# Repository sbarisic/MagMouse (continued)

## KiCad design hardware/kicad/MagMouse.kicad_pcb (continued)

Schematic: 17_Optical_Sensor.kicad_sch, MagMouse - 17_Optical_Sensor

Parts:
C80, C86, C87: 100nF; C_0603_1608Metric; MPN CC0603KRX7R9BB104; LCSC C14663
R131, R135: 10k; R_0603_1608Metric; MPN 0603WAF1002T5E; LCSC C25804
R133, R134, R136: 100k; R_0603_1608Metric; MPN 0603WAF1003T5E; LCSC C25803
TP43: OPT_RESET_N; TestPoint_Pad_D1.0mm
U35: PMW3360DM-T2QU; PixArt_PMW3360DM_T2QU; MPN PMW3360DM-T2QU; LCSC C20612443
U37: SN74LVC125APWR; TSSOP-14_4.4x5mm_P0.65mm; MPN SN74LVC125APWR; LCSC C7813
U39: SN74LVC1G125DBVR; SOT-23-5; MPN SN74LVC1G125DBVR; LCSC C23654

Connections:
CS_PAW: U37.1 (1OE_N), U37.4 (2OE_N), U37.10 (3OE_N), U39.2 (A); also elsewhere on the board
GND: C80.2, C86.2, C87.2, R134.2, U35.8 (GND), U37.7 (GND), U37.13 (4OE_N), U39.1 (OE_N), U39.3 (GND); also elsewhere on the board
OPT_1V9: U35.4 (VDD_1V9); also elsewhere on the board
OPT_3V3: C80.1, C86.1, C87.1, R131.1, R133.1, R135.1, R136.1, U35.5 (VDDIO), U37.14 (VCC), U39.5 (VCC); also elsewhere on the board
OPT_CS_N: R131.2, U35.13 (NCS), U39.4 (Y)
OPT_CTRL: U37.12 (4A); also elsewhere on the board
OPT_LED_P: U35.15 (LED_P); also elsewhere on the board
OPT_MISO: R135.2, U35.12 (MISO), U37.9 (3A)
OPT_MOSI: R134.1, U35.11 (MOSI), U37.3 (1Y)
OPT_RESET_N: TP43.1, U35.7 (NRESET), U37.11 (4Y)
OPT_SCLK: R133.2, U35.10 (SCLK), U37.6 (2Y)
OPT_VDDPIX: U35.3 (VDDPIX_OUT); also elsewhere on the board
PAW_MOTION_N: R136.2, U35.9 (MOTION); also elsewhere on the board
SPI_MISO: U37.8 (3Y); also elsewhere on the board
SPI_MOSI: U37.2 (1A); also elsewhere on the board
SPI_SCLK: U37.5 (2A); also elsewhere on the board

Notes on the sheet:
17 / PMW3360 with selected-device SPI isolation and buffered reset
DRAFT 0.7 - CIRCUIT DEVELOPMENT ONLY - NOT FOR FABRICATION
SPI2 mode 3, <=2MHz. Set SCLK high before selecting; CS setup/read hold/release guard >=1us. U37 disconnects sensor clock, MOSI and MISO while CS_PAW is high; reset channel is always enabled. R72 holds CS high and R79 holds OPT_CTRL low at boot. Keep all CS high during reset and rail transitions. S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
OPT_CTRL low asserts reset despite the internal pull-up (600uA max). U39 isolates CS when unpowered. After valid rails: reset, wait >=50ms, clear motion registers, load authorized SROM and verify identity. Suspend: send Shutdown, deselect, assert reset, clear SENS_REQ. Resume requires full initiali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

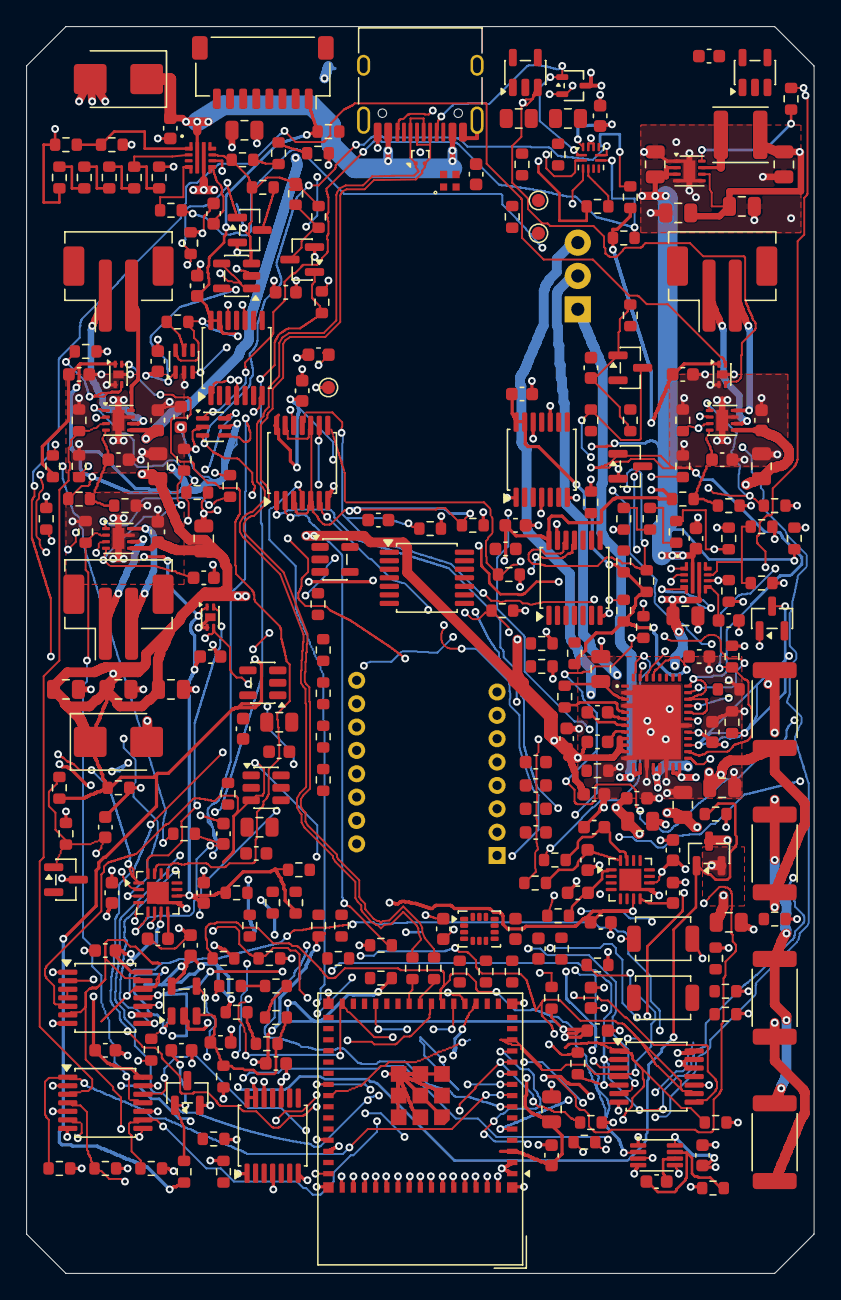
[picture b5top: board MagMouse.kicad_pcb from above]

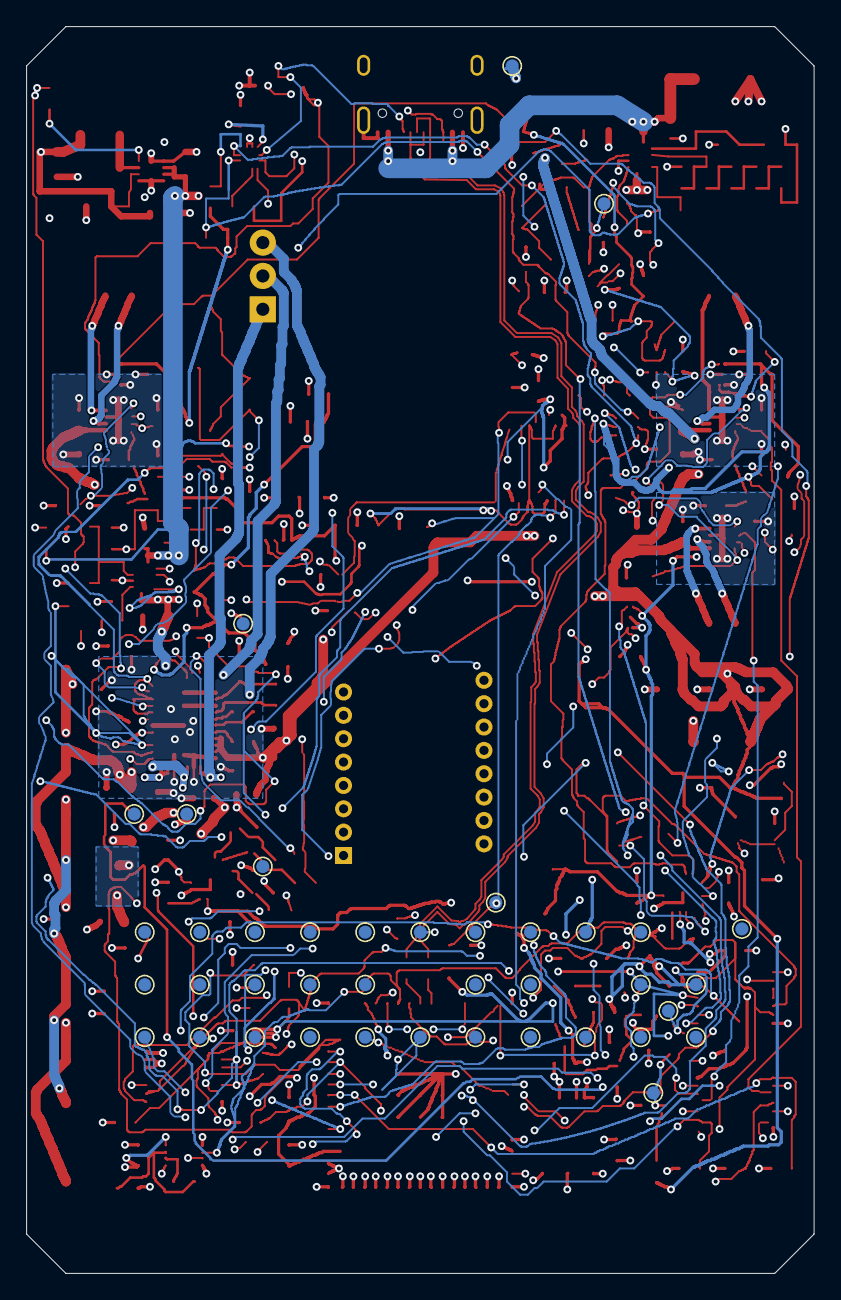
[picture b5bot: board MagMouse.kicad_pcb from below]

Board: 4 copper layers, 60.0 x 95.0 mm, 317 parts (40 on the bottom side), 170 nets.

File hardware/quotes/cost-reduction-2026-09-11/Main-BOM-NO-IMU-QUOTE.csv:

Comment,Designator,Footprint,LCSC Part #,MPN,Quantity
10uF/25V,"C1,C2,C3,C5,C8,C11,C14,C23,C37,C38,C39,C40,C73,C74,C77,C78,C88",Capacitor_SMD:C_0805_2012Metric,C15850,CL21A106KAYNNNE,17
1uF/50V,"C4,C19,C20,C21,C24,C27,C63,C89",Capacitor_SMD:C_0603_1608Metric,C15849,CL10A105KB8NNNC,8
100nF,"C6,C7,C9,C10,C12,C13,C15,C16,C17,C18,C22,C28,C29,C30,C31,C32,C33,C34,C35,C36,C53,C55,C64,C70,C75,C76,C80,C83,C85,C86,C87",Capacitor_SMD:C_0603_1608Metric,C14663,CC0603KRX7R9BB104,31
10nF,"C25,C26",Capacitor_SMD:C_0603_1608Metric,C57112,0603B103K500NT,2
2.2uF/10V,"C71,C81,C82",Capacitor_SMD:C_0603_1608Metric,C100082,CL10B225KP8NNNC,3
10nF,C72,Capacitor_SMD:C_0603_1608Metric,C1589,CL10B103KB8NNNC,1
1nF/50V,C79,Capacitor_SMD:C_0603_1608Metric,C1588,CL10B102KB8NNNC,1
4.7uF/10V,C84,Capacitor_SMD:C_0603_1608Metric,C1705,CL10A475KP8NNNC,1
SMBJ12A,D1,Diode_SMD:D_SMB,C151251,SMBJ12A,1
SMBJ6.0A,D2,Diode_SMD:D_SMB,C83270,SMBJ6.0A,1
BAT54-7-F,"D3,D4",Package_TO_SOT_SMD:SOT-23,C106920,BAT54-7-F,2
SK6805-EC15,D5,MagMouse:OPSCO_SK6805_EC15,C2890035,SK6805-EC15,1
TYPE-C-31-M-12,J1,Connector_USB:USB_C_Receptacle_HRO_TYPE-C-31-M-12,C165948,TYPE-C-31-M-12,1
COIL_L,J2,Connector_JST:JST_PH_B2B-PH-SM4-TB_1x02-1MP_P2.00mm_Vertical,C265003,B2B-PH-SM4-TBT(LF)(SN),1
COIL_M,J3,Connector_JST:JST_PH_B2B-PH-SM4-TB_1x02-1MP_P2.00mm_Vertical,C265003,B2B-PH-SM4-TBT(LF)(SN),1
COIL_R,J4,Connector_JST:JST_PH_B2B-PH-SM4-TB_1x02-1MP_P2.00mm_Vertical,C265003,B2B-PH-SM4-TBT(LF)(SN),1
ENCODER_8P,J6,Connector_JST:JST_SH_SM08B-SRSS-TB_1x08-1MP_P1.00mm_Horizontal,C160407,SM08B-SRSS-TB(LF)(SN),1
WHEEL_SIGNAL_30P,J8,Connector_FFC-FPC:Hirose_FH12-30S-0.5SH_1x30-1MP_P0.50mm_Horizontal,C506793,FH12-30S-0.5SH(55),1
WHEEL_POWER_2P,J10,MagMouseModular:JST_PA_SM02B-PASS_1x02_P2.00mm_Horizontal,C495198,SM02B-PASS-TB(LF)(SN),1
SWPA4020S3R3MT,L1,Inductor_SMD:L_Sunlord_SWPA4020S,C83424,SWPA4020S3R3MT,1
2N7002,"Q1,Q2,Q3",Package_TO_SOT_SMD:SOT-23,C8545,2N7002,3
10k,"R3,R4,R7,R8,R9,R10,R11,R14,R15,R16,R17,R20,R21,R22,R23,R30,R46,R47,R48,R49,R50,R51,R52,R53,R54,R55,R61,R70,R72,R73,R74,R75,R76,R77,R78,R79,R80,R99,R126,R127,R130,R131,R135",Resistor_SMD:R_0603_1608Metric,C25804,0603WAF1002T5E,43
33R,"R5,R6,R58",Resistor_SMD:R_0603_1608Metric,C23140,0603WAF330JT5E,3
3.3k,"R12,R18,R24,R42,R43,R56,R57,R60",Resistor_SMD:R_0603_1608Metric,C22978,0603WAF3301T5E,8
887k,R25,Resistor_SMD:R_0603_1608Metric,C23259,0603WAF8873T5E,1
100k,"R26,R27,R31,R32,R33,R34,R35,R36,R37,R38,R39,R40,R62,R63,R66,R67,R71,R101,R110,R129,R133,R134,R136",Resistor_SMD:R_0603_1608Metric,C25803,0603WAF1003T5E,23
1k,"R28,R44,R45,R64,R69",Resistor_SMD:R_0603_1608Metric,C21190,0603WAF1001T5E,5
22.1k,"R29,R41,R65,R68",Resistor_SMD:R_0603_1608Metric,C25961,0603WAF2212T5E,4
4.7k,R59,Resistor_SMD:R_0603_1608Metric,C23162,0603WAF4701T5E,1
0R,R125,Resistor_SMD:R_0603_1608Metric,C21189,0603WAF0000T5E,1
330R,R128,Resistor_SMD:R_0603_1608Metric,C23138,0603WAF3300T5E,1
39R,R132,Resistor_SMD:R_0603_1608Metric,C23154,0603WAF390JT5E,1
33k,"R141,R142,R143",Resistor_SMD:R_0603_1608Metric,C4216,0603WAF3302T5E,3
RESET,SW1,Button_Switch_SMD:SW_SPST_TS-1088-xR020,C720477,TS-1088-AR02016,1
BOOT,SW2,Button_Switch_SMD:SW_SPST_TS-1088-xR020,C720477,TS-1088-AR02016,1
TPD2EUSB30DRTR,U1,Package_TO_SOT_SMD:Texas_DRT-3,C97502,TPD2EUSB30DRTR,1
TPS62162DSGR,U2,Package_SON:Texas_DSG0008A_WSON-8-1EP_2x2mm_P0.5mm_EP0.9x1.6mm,C40256,TPS62162DSGR,1
ESP32-S3-MINI-1-N8,U3,RF_Module:ESP32-S2-MINI-1,C2913206,ESP32-S3-MINI-1-N8,1
DRV8231ADSGR,"U4,U5,U6",Package_SON:Texas_DSG0008A_WSON-8-1EP_2x2mm_P0.5mm_EP0.9x1.6mm,C5139865,DRV8231ADSGR,3
TMAG5253BA2IQDMRR,"U7,U8,U9",Package_SON:Texas_X2SON-4-1EP_1.1x1.4mm_P0.5mm_EP0.8x0.6mm,C35414983,TMAG5253BA2IQDMRR,3
ADS7038IRTER,U10,Package_DFN_QFN:WQFN-16-1EP_3x3mm_P0.5mm_EP1.68x1.68mm,C2871580,ADS7038IRTER,1
TUSB320LAIRWBR,U11,Package_DFN_QFN:Texas_X2QFN-12_1.6x1.6mm_P0.4mm,C132554,TUSB320LAIRWBR,1
TPS259470LRPWR,"U12,U13",MagMouse:Texas_RPW0010A,C3662793,TPS259470LRPWR,2
SN74LVC2G04DCKR,U14,Package_TO_SOT_SMD:SOT-363_SC-70-6,C105251,SN74LVC2G04DCKR,1
SN74LVC1G123DCUR,U15,Package_SO:VSSOP-8_2.3x2mm_P0.5mm,C352969,SN74LVC1G123DCUR,1
SN74LVC08APWR,"U16,U17,U18",Package_SO:TSSOP-14_4.4x5mm_P0.65mm,C465737,SN74LVC08APWR,3
TLV9001IDBVR,U19,Package_TO_SOT_SMD:SOT-23-5,C398363,TLV9001IDBVR,1
TPD2E2U06DCKR,U20,Package_TO_SOT_SMD:SOT-323_SC-70,C1855726,TPD2E2U06DCKR,1
SN74LVC125APWR,"U25,U29,U37",Package_SO:TSSOP-14_4.4x5mm_P0.65mm,C7813,SN74LVC125APWR,3
TPS22919DCKR,U28,Package_TO_SOT_SMD:SOT-363_SC-70-6,C2149796,TPS22919DCKR,1
TPS7A2450DBVR,U33,Package_TO_SOT_SMD:SOT-23-5,C2864436,TPS7A2450DBVR,1
SN74LV1T34DBVR,U34,Package_TO_SOT_SMD:SOT-23-5,C100024,SN74LV1T34DBVR,1
TLV75519PDBVR,U36,Package_TO_SOT_SMD:SOT-23-5,C2865381,TLV75519PDBVR,1
TPS22918DBVR,U38,Package_TO_SOT_SMD:SOT-23-6,C131941,TPS22918DBVR,1
SN74LVC1G125DBVR,U39,Package_TO_SOT_SMD:SOT-23-5,C23654,SN74LVC1G125DBVR,1

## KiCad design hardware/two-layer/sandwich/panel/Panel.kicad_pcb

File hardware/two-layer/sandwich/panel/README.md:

# Four-board quotation panel

One 238 × 114 mm, two-layer panel contains one Lower, Upper, Wheel and Encoder
board. Five panels provide five complete sets. The individual board outlines,
component positions and copper are preserved by translation; nets are isolated
between boards. The panel uses 2 mm routed gaps, 5 mm tabs and 0.6 mm mousebites
on 0.9 mm pitch. The drill row lies outside each finished board outline.

Upload `MagMouse-panel-gerbers.zip` as **Panel by Customer**, **4 designs**,
**5 panels**, FR4, 1.6 mm, 1 oz, green/white, ENIG 1 µin, 0.30 mm minimum via
drill and tented vias. Components, assembly and stencil are separate.

`panelize.py` generates this folder from the four individual boards and checks
exact translated pads, traces, drills and filled copper; connected substrate;
router access; and native KiCad DRC. `panel-manifest.json` records source hashes.
The individual boards also pass ERC, DRC and schematic parity checks, with zero
unconnected nets and zero via-hole/SMD-pad intersections.

This is a quotation package. Supplier CAM approval and prototype electrical,
thermal and enclosure-fit checks remain necessary before production release.

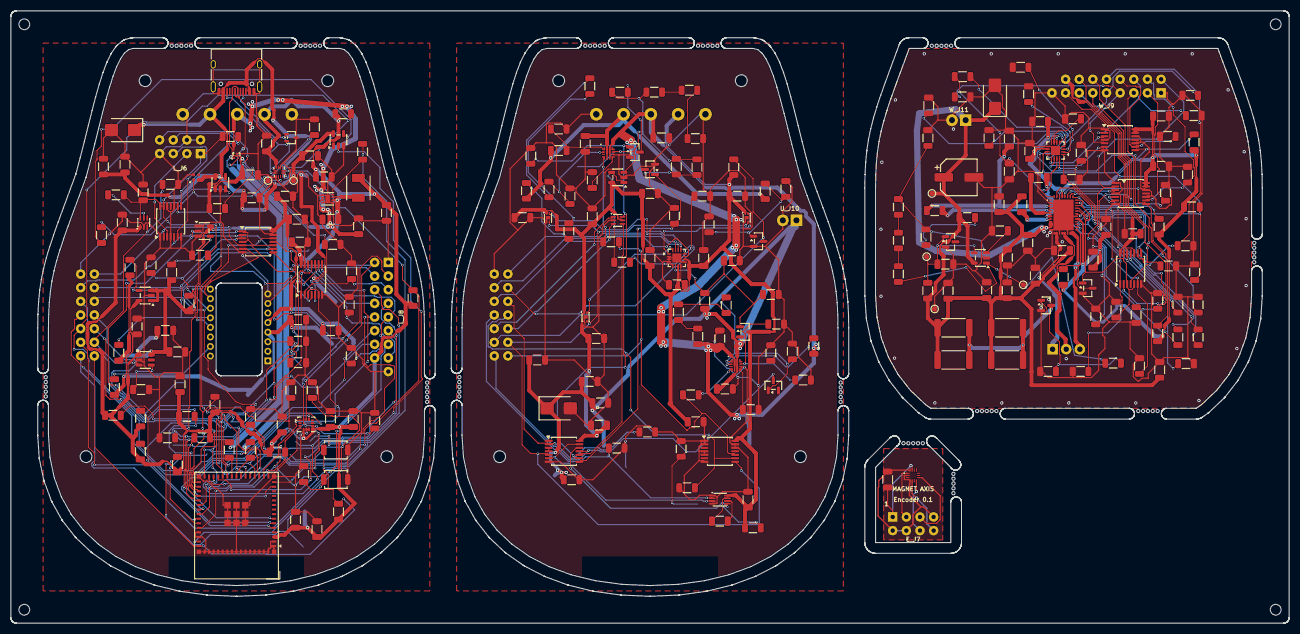
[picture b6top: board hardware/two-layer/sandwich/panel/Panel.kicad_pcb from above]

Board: 2 copper layers, 238.0 x 114.0 mm, 384 parts (37 on the bottom side), 186 nets.

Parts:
E_C62: 1uF/50V; C_1206_3216Metric
E_J7: Soldered wires Signal_2x04; Wire_Signal_2x04_P2.54mm
E_U27: MA735GGU-P; MPS_UTQFN14_2x2
L_C1, L_C2, L_C3, L_C5, L_C23, L_C73, L_C74, L_C77, L_C78: 10uF/25V; C_1206_3216Metric
L_C4, L_C63: 1uF/50V; C_1206_3216Metric
L_C6, L_C22, L_C53, L_C55, L_C64, L_C70, L_C75, L_C76, L_C80, L_C83, L_C85, L_C86, L_C87: 100nF; C_1206_3216Metric
L_C71, L_C81, L_C82: 2.2uF/10V; C_1206_3216Metric
L_C72: 10nF; C_1206_3216Metric_OneSideSilk
L_C79: 1nF/50V; C_1206_3216Metric
L_C84: 4.7uF/10V; C_1206_3216Metric
L_D1: SMBJ12A; D_SMB
L_D5: SK6805-EC15; OPSCO_SK6805_EC15
L_H101, L_H102, L_H103, L_H104: M2 clearance / 5mm support envelope; MountingHole_2.2mm_M2_5mm_Envelope
L_J1: TYPE-C-31-M-12; USB_C_Receptacle_HRO_TYPE-C-31-M-12
L_J6: Soldered wires Signal_2x04; Wire_Signal_2x04_P2.54mm
L_J8: Wheel 17-wire signals / 2 GND; Wire_Wheel_17_P2.54mm
L_J101: Stack signals / 14 wires; Wire_Stack_Signal_14
L_J103: Stack power / 5 wires; Wire_Stack_Power_5
L_L1: SRP4020CC-3R3M; L_Bourns_SRP4020CC
L_R3, L_R4, L_R7, L_R72, L_R73, L_R74, L_R75, L_R76, L_R77, L_R78, L_R79, L_R80, L_R99, L_R126, L_R127, L_R130, L_R131, L_R135: 10k; R_1206_3216Metric
L_R5, L_R6: 33R; R_1206_3216Metric
L_R25: 887k; R_1206_3216Metric
L_R26, L_R27, L_R101, L_R110, L_R129, L_R133, L_R134, L_R136: 100k; R_1206_3216Metric
L_R28: 1k; R_1206_3216Metric
L_R125: 0R; R_1206_3216Metric
L_R128: 330R; R_1206_3216Metric
L_R132: 39R; R_1206_3216Metric
L_R141, L_R142, L_R143: 33k; R_1206_3216Metric
L_SW1: RESET; SW_SPST_TS-1088-xR020
L_SW2: BOOT; SW_SPST_TS-1088-xR020
L_TP1, L_TP10: VBUS_USB; TestPoint_Pad_D1.0mm
L_TP4: UART_TX; TestPoint_Pad_D1.0mm
L_TP5: UART_RX; TestPoint_Pad_D1.0mm
L_TP6: MCU_EN; TestPoint_Pad_D1.0mm
L_TP7: BOOT; TestPoint_Pad_D1.0mm
L_TP8: +3V3; TestPoint_Pad_D1.0mm
L_TP9: GND; TestPoint_Pad_D1.0mm
L_TP16: CS_PAW; TestPoint_Pad_D1.0mm
L_TP17: WHEEL_RUN_REQ; TestPoint_Pad_D1.0mm
L_TP18: CS_IMU; TestPoint_Pad_D1.0mm
L_TP19: OPT_CTRL; TestPoint_Pad_D1.0mm
L_TP20: MOTOR_SPI_MOSI; TestPoint_Pad_D1.0mm
L_TP21: MOTOR_SPI_SCLK; TestPoint_Pad_D1.0mm
L_TP22: MOTOR_SPI_MISO; TestPoint_Pad_D1.0mm
L_TP23: CS_ADC2; TestPoint_Pad_D1.0mm
L_TP24: CS_MA735; TestPoint_Pad_D1.0mm
L_TP25: CS_DRV8316; TestPoint_Pad_D1.0mm
L_TP26: PAW_MOTION_N; TestPoint_Pad_D1.0mm
L_TP27: IMU_INT1; TestPoint_Pad_D1.0mm
L_TP28: DRV_FAULT_N; TestPoint_Pad_D1.0mm
L_TP29: WHEEL_PWM_A; TestPoint_Pad_D1.0mm
L_TP30: RGB_DATA; TestPoint_Pad_D1.0mm
L_TP31: BOOT_SAFE_SPARE; TestPoint_Pad_D1.0mm
L_TP32: WHEEL_PWM_B; TestPoint_Pad_D1.0mm
L_TP33: WHEEL_PWM_C; TestPoint_Pad_D1.0mm
L_TP38: RGB_5V; TestPoint_Pad_D1.0mm
L_TP39: RGB_DIN; TestPoint_Pad_D1.0mm
L_TP40: OPT_3V3; TestPoint_Pad_D1.0mm
L_TP41: OPT_1V9; TestPoint_Pad_D1.0mm
L_TP42: OPT_VDDPIX; TestPoint_Pad_D1.0mm
L_TP43: OPT_RESET_N; TestPoint_Pad_D1.0mm
L_U1: TPD2EUSB30DRTR; Texas_DRT-3
L_U2: TPS62162DSGR; Texas_DSG0008A_WSON-8-1EP_2x2mm_P0.5mm_EP0.9x1.6mm
L_U3: ESP32-S3-MINI-1-N8; ESP32-S2-MINI-1
L_U11: TUSB320LAIRWBR; Texas_X2QFN-12_1.6x1.6mm_P0.4mm
L_U20: TPD2E2U06DCKR; SOT-323_SC-70
L_U25, L_U29, L_U37: SN74LVC125APWR; TSSOP-14_4.4x5mm_P0.65mm
L_U28: TPS22919DCKR; SOT-363_SC-70-6
L_U32: ICM-42688-P; LGA-14_3x2.5mm_P0.5mm_LayoutBorder3x4y
L_U33: TPS7A2450DBVR; SOT-23-5
L_U34: SN74LV1T34DBVR; SOT-23-5
L_U35: PMW3360DM-T2QU; PixArt_PMW3360DM_T2QU
L_U36: TLV75519PDBVR; SOT-23-5
L_U38: TPS22918DBVR; SOT-23-6
L_U39: SN74LVC1G125DBVR; SOT-23-5
MB1_1, MB1_2, MB1_3, MB1_4, MB1_5, MB2_1, MB2_2, MB2_3, MB2_4, MB2_5, MB3_1, MB3_2, MB3_3, MB3_4, MB3_5, MB4_1, MB4_2, MB4_3, MB4_4, MB4_5, MB5_1, MB5_2, MB5_3, MB5_4, MB5_5, MB6_1, MB6_2, MB6_3, MB6_4, MB6_5, MB7_1, MB7_2, MB7_3, MB7_4, MB7_5, MB8_1, MB8_2, MB8_3, MB8_4, MB8_5, MB9_1, MB9_2, MB9_3, MB9_4, MB9_5, MB10_1, MB10_2, MB10_3, MB10_4, MB10_5, MB11_1, MB11_2, MB11_3, MB11_4, MB11_5, MB12_1, MB12_2, MB12_3, MB12_4, MB12_5, MB13_1, MB13_2, MB13_3, MB13_4, MB13_5, MB14_1, MB14_2, MB14_3, MB14_4, MB14_5: NPTH
TOOL1, TOOL2, TOOL3, TOOL4: NPTH
U_C16, U_C17, U_C18, U_C28, U_C29, U_C31, U_C32, U_C33, U_C34, U_C35, U_C36: 100nF; C_1206_3216Metric
U_C19, U_C20, U_C21, U_C24, U_C27, U_C89: 1uF/50V; C_1206_3216Metric
U_C25, U_C26: 10nF; C_1206_3216Metric
U_C37, U_C38, U_C39, U_C40, U_C88: 10uF/25V; C_1206_3216Metric
U_D2: SMBJ6.0A; D_SMB
U_D3, U_D4: BAT54-7-F; SOT-23
U_H105, U_H106, U_H107, U_H108: M2 clearance / 5mm support envelope; MountingHole_2.2mm_M2_5mm_Envelope
U_J10: Soldered wires Power_1x02; Wire_Power_1x02_P2.54mm
U_J102: Stack signals / 14 wires; Wire_Stack_Signal_14
U_J104: Stack power / 5 wires; Wire_Stack_Power_5
U_Q1, U_Q2, U_Q3: 2N7002; SOT-23
U_R29, U_R41, U_R65, U_R68: 22.1k; R_1206_3216Metric
U_R30, U_R46, U_R47, U_R48, U_R49, U_R61, U_R70: 10k; R_1206_3216Metric
U_R31, U_R32, U_R33, U_R34, U_R35, U_R36, U_R37, U_R38, U_R39, U_R40, U_R62, U_R63, U_R66, U_R67, U_R71: 100k; R_1206_3216Metric
U_R42, U_R43, U_R56, U_R57, U_R60: 3.3k; R_1206_3216Metric
U_R44, U_R45, U_R64, U_R69: 1k; R_1206_3216Metric
U_R58: 33R; R_1206_3216Metric
U_R59: 4.7k; R_1206_3216Metric
U_TP2, U_TP11: PWR_5V; TestPoint_Pad_D1.0mm
U_TP3, U_TP12: ACT_5V; TestPoint_Pad_D1.0mm
U_TP13: ACT_DRIVE_EN; TestPoint_Pad_D1.0mm
U_TP14: USB_ILM; TestPoint_Pad_D1.0mm
U_TP15: GND; TestPoint_Pad_D1.0mm
U_U7, U_U8, U_U9: TMAG5253BA2IQDMRR; Texas_X2SON-4-1EP_1.1x1.4mm_P0.5mm_EP0.8x0.6mm
U_U10: ADS7038IRTER; WQFN-16-1EP_3x3mm_P0.5mm_EP1.68x1.68mm
U_U12, U_U13: TPS259470LRPWR; Texas_RPW0010A
U_U14: SN74LVC2G04DCKR; SOT-363_SC-70-6
U_U15: SN74LVC1G123DCUR; VSSOP-8_2.3x2mm_P0.5mm
U_U16, U_U18: SN74LVC08APWR; TSSOP-14_4.4x5mm_P0.65mm
U_U19: TLV9001IDBVR; SOT-23-5
W_C41, W_C42, W_C43, W_C49, W_C51, W_C52, W_C54, W_C65, W_C66: 100nF; C_1206_3216Metric
W_C44, W_C45, W_C68, W_C69: 10uF/25V; C_1206_3216Metric
W_C46, W_C48, W_C56, W_C57, W_C58: 1uF/50V; C_1206_3216Metric
W_C47: 47nF/50V; C_1206_3216Metric
W_C50: 22uF/25V; C_1206_3216Metric
W_C59, W_C60, W_C61, W_C67: 22pF/50V; C_1206_3216Metric
W_C90: 100uF/16V; CP_Elec_6.3x5.9
W_D6: SMBJ6.0A; D_SMB
W_J5: GB1806 phase wires; MotorWire_3x1mm_P2.54mm
W_J9: Wheel 17-wire signals / 2 GND; Wire_Wheel_17_P2.54mm
W_J11: Soldered wires Power_1x02; Wire_Power_1x02_P2.54mm
W_Q4: 2N7002; SOT-23
W_Q5: AO3400A; SOT-23
W_R81: 22R; R_1206_3216Metric
W_R82, W_R84, W_R86, W_R98, W_R111, W_R137, W_R138, W_R139, W_R140: 10k; R_1206_3216Metric
W_R83, W_R89, W_R90, W_R91, W_R92, W_R94, W_R95, W_R96, W_R97, W_R100, W_R112, W_R114, W_R120: 100k; R_1206_3216Metric
W_R87, W_R88, W_R146: 4.7k; R_1206_3216Metric
W_R102, W_R103, W_R104: 330R; R_1206_3216Metric
W_R105, W_R106, W_R107, W_R108, W_R109: 0R; R_1206_3216Metric
W_R113: 34.8k; R_1206_3216Metric
W_R115, W_R116, W_R117: 1M; R_1206_3216Metric
W_R119: 100R; R_1206_3216Metric
W_R121, W_R122, W_R123, W_R124: 47R/2W; R_2512_6332Metric
W_R144, W_R145: 33k; R_1206_3216Metric
W_TP34: ACT_5V; TestPoint_Pad_D1.0mm
W_TP35: BRAKE_REF; TestPoint_Pad_D1.0mm
W_TP36: BRAKE_OUT; TestPoint_Pad_D1.0mm
W_TP37: GND; TestPoint_Pad_D1.0mm
W_U21: DRV8316RRGFR; Texas_RGF0040E
W_U22: SN74LVC08APWR; TSSOP-14_4.4x5mm_P0.65mm
W_U23: ADS7038IRTER; WQFN-16-1EP_3x3mm_P0.5mm_EP1.68x1.68mm
W_U24: SN74LVC125APWR; TSSOP-14_4.4x5mm_P0.65mm_InsetPin1
W_U26: SN74LVC125APWR; TSSOP-14_4.4x5mm_P0.65mm
W_U30: TLV1811DBVR; SOT-23-5
W_U31: LM4040AIM3-2.5/NOPB; SOT-23

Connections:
Encoder/ENC_3V3: E_C62.1, E_J7.1, E_U27.13
Encoder/ENC_CS_LOCAL: E_J7.6, E_U27.7
Encoder/ENC_MISO_LOCAL: E_J7.8, E_U27.5
Encoder/ENC_MOSI_LOCAL: E_J7.5, E_U27.8
Encoder/ENC_SCLK_LOCAL: E_J7.3, E_U27.1
Encoder/GND: E_C62.2, E_J7.2, E_J7.4, E_J7.7, E_U27.2, E_U27.4, E_U27.14
Lower/+3V3: L_C2.1, L_C3.1, L_C5.1, L_C6.1, L_C22.1, L_C23.1, L_C53.1, L_C63.1, L_C70.1, L_C71.1, L_C72.1, L_C77.1, L_C78.1, L_J8.16, L_J103.4, L_L1.2, L_R3.1, L_R4.1, L_R7.1, L_R26.1, L_R27.1, L_R72.1, L_R73.1, L_R74.1, L_R75.1, L_R76.1, L_R127.1, L_TP8.1, L_U2.6, L_U3.3, L_U11.12, L_U25.14, L_U28.1, L_U32.5, L_U32.8, L_U38.1
Lower/ACT_DRIVE_EN: L_J8.13, L_J101.13
Lower/ACT_HEARTBEAT: L_J101.7, L_U3.21
Lower/ACT_REQ: L_J101.6, L_U3.20
Lower/ADC2_MISO_LOCAL: L_J8.9, L_R143.1, L_U25.9
Lower/ADC_CS: L_J101.5, L_R7.2, L_U3.14
Lower/BOOT: L_R4.2, L_SW2.1, L_TP7.1, L_U3.4
Lower/BOOT_SAFE_SPARE: L_R80.1, L_TP31.1, L_U3.44
Lower/BUCK_SW: L_L1.1, L_U2.7
Lower/CC_OUT1: L_J101.9, L_R26.2, L_U3.18, L_U11.7
Lower/CC_OUT2: L_J101.10, L_R27.2, L_U3.19, L_U11.8
Lower/CC_VBUS_DET: L_R25.2, L_U11.4
Lower/CS_ADC2: L_J8.8, L_R74.2, L_TP23.1, L_U3.32, L_U25.10
Lower/CS_DRV8316: L_J8.4, L_R76.2, L_TP25.1, L_U3.34, L_U25.1
Lower/CS_IMU: L_R73.2, L_TP18.1, L_U3.25, L_U32.12
Lower/CS_MA735: L_R75.2, L_TP24.1, L_U3.33, L_U25.4, L_U29.9
Lower/CS_PAW: L_R72.2, L_TP16.1, L_U3.6, L_U37.1, L_U37.4, L_U37.10, L_U39.2
Lower/DRV_FAULT_LOCAL_N: L_J8.15, L_R141.1, L_U25.12
Lower/DRV_FAULT_N: L_TP28.1, L_U3.37, L_U25.11
Lower/DRV_MISO_LOCAL: L_J8.5, L_R142.1, L_U25.2
Lower/ENC_3V3: L_C55.1, L_C64.1, L_J6.1, L_R99.1, L_R125.2, L_U28.6, L_U29.13, L_U29.14
Lower/ENC_CS_LOCAL: L_J6.6, L_R99.2, L_U29.8
Lower/ENC_MISO_LOCAL: L_J6.8, L_R101.1, L_U25.5
Lower/ENC_MOSI_LOCAL: L_J6.5, L_U29.6
Lower/ENC_QOD: L_R125.1, L_U28.5
Lower/ENC_SCLK_LOCAL: L_J6.3, L_U29.3
Lower/GND: L_C1.2, L_C2.2, L_C3.2, L_C4.2, L_C5.2, L_C6.2, L_C22.2, L_C23.2, L_C53.2, L_C55.2, L_C63.2, L_C64.2, L_C70.2, L_C71.2, L_C72.2, L_C73.2, L_C74.2, L_C75.2, L_C76.2, L_C77.2, L_C78.2, L_C79.2, L_C80.2, L_C81.2, L_C82.2, L_C83.2, L_C84.2, L_C85.2, L_C86.2, L_C87.2, L_D1.2, L_D5.4, L_J1.A1, L_J1.A12, L_J1.B1, L_J1.B12, L_J1.SH, L_J6.2, L_J6.4, L_J6.7, L_J8.1, L_J8.17, L_J101.1, L_J103.1, L_J103.5, L_R77.2, L_R78.2, L_R79.2, L_R80.2, L_R101.2, L_R110.2, L_R126.2, L_R129.2, L_R130.2, L_R134.2, L_R141.2, L_R142.2, L_R143.2, L_SW1.2, L_SW2.2, L_TP9.1, L_U1.3, L_U2.1, L_U2.4, L_U2.5, L_U2.9, L_U3.1, L_U3.2, L_U3.42, L_U3.43, L_U3.46, L_U3.47, L_U3.48, L_U3.49, L_U3.50, L_U3.51, L_U3.52, L_U3.53, L_U3.54, L_U3.55, L_U3.56, L_U3.57, L_U3.58, L_U3.59, L_U3.60, L_U3.61, L_U3.62, L_U3.63, L_U3.64, L_U3.65, L_U11.3, L_U11.10, L_U11.11, L_U20.3, L_U25.7, L_U25.13, L_U28.2, L_U29.1, L_U29.4, L_U29.7, L_U29.10, L_U29.12, L_U32.6, L_U32.7, L_U33.2, L_U34.3, L_U35.8, L_U36.2, L_U37.7, L_U37.13, L_U38.2, L_U39.1, L_U39.3
Lower/HALL_EN: L_J101.12, L_R110.1, L_U28.3, L_U33.3, L_U38.3
Lower/IMU_INT1: L_R127.2, L_TP27.1, L_U3.36, L_U32.4
Lower/IMU_PIN9: L_R126.1, L_U32.9
Lower/LOGIC_PG: L_R28.1, L_U2.8
Lower/MCU_EN: L_C4.1, L_J101.14, L_R3.2, L_R28.2, L_SW1.1, L_TP6.1, L_U3.45
Lower/MCU_USB_DM: L_R5.1, L_U3.23
Lower/MCU_USB_DP: L_R6.1, L_U3.24
Lower/MOTOR_SPI_MISO: L_TP22.1, L_U3.31, L_U25.8
Lower/MOTOR_SPI_MOSI: L_J8.7, L_TP20.1, L_U3.28
Lower/MOTOR_SPI_SCLK: L_J8.6, L_TP21.1, L_U3.29
Lower/OPT_1V9: L_C82.1, L_C83.1, L_R132.1, L_TP41.1, L_U35.4, L_U36.5
Lower/OPT_3V3: L_C80.1, L_C81.1, L_C86.1, L_C87.1, L_R131.1, L_R133.1, L_R135.1, L_R136.1, L_TP40.1, L_U35.5, L_U36.1, L_U36.3, L_U37.14, L_U38.6, L_U39.5
Lower/OPT_CS_N: L_R131.2, L_U35.13, L_U39.4
Lower/OPT_CTRL: L_R79.1, L_TP19.1, L_U3.26, L_U37.12
Lower/OPT_LED_P: L_R132.2, L_U35.15
Lower/OPT_MISO: L_R135.2, L_U35.12, L_U37.9
Lower/OPT_MOSI: L_R134.1, L_U35.11, L_U37.3
Lower/OPT_RAMP_CT: L_C79.1, L_U38.4
Lower/OPT_RESET_N: L_TP43.1, L_U35.7, L_U37.11
Lower/OPT_SCLK: L_R133.2, L_U35.10, L_U37.6
Lower/OPT_VDDPIX: L_C84.1, L_C85.1, L_TP42.1, L_U35.3
Lower/PAW_MOTION_N: L_R136.2, L_TP26.1, L_U3.35, L_U35.9
Lower/PWR_5V: L_C1.1, L_C73.1, L_J103.3, L_U2.2, L_U2.3, L_U33.1
Lower/RGB_5V: L_C74.1, L_C75.1, L_C76.1, L_D5.2, L_R130.1, L_TP38.1, L_U33.5, L_U34.5
Lower/RGB_BUFFER_OUT: L_R128.1, L_U34.4
Lower/RGB_DATA: L_R78.1, L_TP30.1, L_U3.41, L_U34.2
Lower/RGB_DIN: L_D5.1, L_R128.2, L_R129.1, L_TP39.1
Lower/SENS_REQ: L_J101.8, L_U3.22
Lower/SPI_MISO: L_J101.4, L_U3.17, L_U25.3, L_U25.6, L_U32.1, L_U37.8
Lower/SPI_MOSI: L_J8.3, L_J101.3, L_U3.15, L_U29.5, L_U32.14, L_U37.2
Lower/SPI_SCLK: L_J8.2, L_J101.2, L_U3.16, L_U29.2, L_U32.13, L_U37.5
Lower/UART_RX: L_TP5.1, L_U3.40
Lower/UART_TX: L_TP4.1, L_U3.39
Lower/USB_CC1: L_J1.A5, L_U11.1, L_U20.1
Lower/USB_CC2: L_J1.B5, L_U11.2, L_U20.2
Lower/USB_DM: L_J1.A7, L_J1.B7, L_R5.2, L_U1.2
Lower/USB_DP: L_J1.A6, L_J1.B6, L_R6.2, L_U1.1
Lower/VBUS_PRESENT_N: L_J101.11, L_U3.5
Lower/VBUS_USB: L_D1.1, L_J1.A4, L_J1.A9, L_J1.B4, L_J1.B9, L_J103.2, L_R25.1, L_TP1.1, L_TP10.1
Lower/WHEEL_PWM_A: L_J8.10, L_TP29.1, L_U3.38
Lower/WHEEL_PWM_B: L_J8.11, L_TP32.1, L_U3.27
Lower/WHEEL_PWM_C: L_J8.12, L_TP33.1, L_U3.30
Lower/WHEEL_RUN_REQ: L_J8.14, L_R77.1, L_TP17.1, L_U3.7
Upper/+3V3: U_C16.1, U_C17.1, U_C18.1, U_C19.1, U_C20.1, U_C28.1, U_C29.1, U_C31.1, U_C32.1, U_C34.1, U_D4.3, U_J104.4, U_R46.1, U_R71.1, U_U7.1, U_U8.1, U_U9.1, U_U10.7, U_U10.10, U_U14.5, U_U15.8, U_U16.14, U_U18.14, U_U19.5
Upper/ACT_5V: U_C37.1, U_C38.1, U_C39.1, U_C40.1, U_D2.1, U_J10.1, U_R67.1, U_R69.1, U_TP3.1, U_TP12.1, U_U13.6
Upper/ACT_DRIVE_EN: U_D3.3, U_J102.13, U_R49.1, U_TP13.1, U_U16.11
Upper/ACT_DVDT: U_C26.1, U_U13.7
Upper/ACT_FAULT_N: U_R45.1, U_U13.4
Upper/ACT_HEARTBEAT: U_J102.7, U_R47.1, U_U15.2
Upper/ACT_ILM: U_R42.1, U_R43.1, U_U13.9
Upper/ACT_OVLO: U_R40.2, U_R41.1, U_U13.2
Upper/ACT_PERMIT: U_U15.5, U_U16.12
Upper/ACT_REQ: U_J102.6, U_R48.1, U_U16.2
Upper/ACT_UVLO: U_D3.1, U_R38.2, U_R39.1, U_U13.1
Upper/ACT_UV_1: U_R36.2, U_R37.1
Upper/ACT_UV_2: U_R37.2, U_R38.1
Upper/ACT_VMON: U_C36.1, U_D4.1, U_R67.2, U_R68.1, U_U10.6
Upper/ADC_CS: U_J102.5, U_U10.11
Upper/ADC_DECAP: U_C21.1, U_U10.8
Upper/ARM_SOURCE: U_U16.3, U_U16.4
Upper/ARM_VALID: U_U15.3, U_U16.6, U_U16.13
Upper/CC_OUT1: U_J102.9, U_U14.1
Upper/CC_OUT2: U_J102.10, U_U14.3
Upper/CC_OUT2_INV: U_U14.4, U_U16.10
Upper/GND: U_C16.2, U_C17.2, U_C18.2, U_C19.2, U_C20.2, U_C21.2, U_C24.2, U_C25.2, U_C26.2, U_C28.2, U_C29.2, U_C31.2, U_C32.2, U_C33.2, U_C34.2, U_C35.2, U_C36.2, U_C37.2, U_C38.2, U_C39.2, U_C40.2, U_C88.2, U_C89.2, U_D2.2, U_J10.2, U_J102.1, U_J104.1, U_J104.5, U_Q1.2, U_Q2.2, U_Q3.2, U_R30.2, U_R35.2, U_R39.2, U_R41.2, U_R42.2, U_R43.2, U_R47.2, U_R48.2, U_R49.2, U_R58.2, U_R62.2, U_R63.2, U_R66.2, U_R68.2, U_R69.2, U_R70.2, U_TP15.1, U_U7.2, U_U7.5, U_U8.2, U_U8.5, U_U9.2, U_U9.5, U_U10.2, U_U10.3, U_U10.4, U_U10.9, U_U10.17, U_U12.8, U_U13.8, U_U14.2, U_U15.1, U_U15.4, U_U16.7, U_U18.1, U_U18.2, U_U18.4, U_U18.5, U_U18.7, U_U18.12, U_U18.13, U_U19.2
Upper/HALL_EN: U_J102.12, U_U7.3, U_U8.3, U_U9.3, U_U16.5, U_U18.8
Upper/HALL_L: U_U7.4, U_U10.15
Upper/HALL_M: U_U8.4, U_U10.16
Upper/HALL_R: U_U9.4, U_U10.1
Upper/ILM_BASE_1: U_R56.2, U_R57.1
Upper/ILM_BASE_2: U_R57.2, U_R58.1
Upper/ILM_HIGH_D: U_Q2.3, U_R60.2, U_R61.2
Upper/ILM_MED_D: U_Q1.3, U_R59.2
Upper/MCU_EN: U_J102.14, U_R44.2, U_R45.2, U_U18.10
Upper/PWR_5V: U_C88.1, U_C89.1, U_J104.3, U_R36.1, U_R40.1, U_TP2.1, U_TP11.1, U_U12.6, U_U13.5
Upper/SENS_REQ: U_J102.8, U_R70.1, U_U18.9
Upper/SOURCE_3A: U_Q2.1, U_R63.1, U_U16.8
Upper/SOURCE_OK: U_Q1.1, U_R62.1, U_U14.6, U_U16.1, U_U16.9
Upper/SPI_MISO: U_J102.4, U_U10.12
Upper/SPI_MOSI: U_J102.3, U_U10.14
Upper/SPI_SCLK: U_J102.2, U_U10.13
Upper/USB_DVDT: U_C25.1, U_U12.7
Upper/USB_FAULT_N: U_R44.1, U_U12.4
Upper/USB_ILM: U_R56.1, U_R59.1, U_R60.1, U_R61.1, U_TP14.1, U_U12.9, U_U19.3
Upper/USB_IMON_ADC: U_C33.1, U_R64.2, U_U10.5
Upper/USB_IMON_BUF: U_R64.1, U_U19.1, U_U19.4
Upper/USB_OVLO: U_R34.2, U_R35.1, U_U12.2
Upper/USB_OV_1: U_R31.2, U_R32.1
Upper/USB_OV_2: U_R32.2, U_R33.1
Upper/USB_OV_3: U_R33.2, U_R34.1
Upper/USB_UVLO: U_R29.2, U_R30.1, U_U12.1
Upper/VBUS_GATE: U_C35.1, U_Q3.1, U_R65.2, U_R66.1
Upper/VBUS_PRESENT_N: U_J102.11, U_Q3.3, U_R71.2
Upper/VBUS_USB: U_C24.1, U_J104.2, U_R29.1, U_R31.1, U_R65.1, U_U12.5
Upper/WD_CEXT: U_C27.2, U_U15.6
Upper/WD_RCEXT: U_C27.1, U_R46.2, U_U15.7
Wheel/+3V3: W_C51.1, W_J9.16, W_U22.14
Wheel/ACT_5V: W_C41.1, W_C42.1, W_C43.1, W_C44.1, W_C45.1, W_C46.2, W_C65.1, W_C68.1, W_C69.1, W_C90.1, W_D6.1, W_J11.1, W_R111.1, W_R112.1, W_R121.1, W_R122.1, W_R123.1, W_R124.1, W_R146.1, W_TP34.1, W_U21.9, W_U21.10, W_U21.11, W_U30.5
Wheel/ACT_DRIVE_EN: W_J9.13, W_R84.1, W_U21.23, W_U22.1
Wheel/ADC2_CS_LOCAL: W_R98.2, W_U23.11, W_U26.8
Wheel/ADC2_DECAP: W_C58.1, W_U23.8
Wheel/ADC2_MISO_LOCAL: W_J9.9, W_R100.1, W_U23.12
Wheel/ADC2_MOSI_LOCAL: W_U23.14, W_U26.6
Wheel/ADC2_SCLK_LOCAL: W_U23.13, W_U26.3
Wheel/ADC2_SPARE3: W_R105.1, W_U23.2
Wheel/ADC2_SPARE4: W_R106.1, W_U23.3
Wheel/ADC2_SPARE5: W_R107.1, W_U23.4
Wheel/ADC2_SPARE6: W_R108.1, W_U23.5
Wheel/ADC2_SPARE7: W_R109.1, W_U23.6
Wheel/BRAKE_DIV_TOP: W_R112.2, W_R113.1
Wheel/BRAKE_DRAIN: W_Q5.3, W_R121.2, W_R122.2, W_R123.2, W_R124.2
Wheel/BRAKE_FB_1: W_R115.2, W_R116.1
Wheel/BRAKE_FB_2: W_R116.2, W_R117.1
Wheel/BRAKE_GATE: W_Q5.1, W_R119.2, W_R120.1
Wheel/BRAKE_OUT: W_R115.1, W_R119.1, W_TP36.1, W_U30.1
Wheel/BRAKE_REF: W_C66.1, W_R111.2, W_TP35.1, W_U30.4, W_U31.1
Wheel/BRAKE_SENSE: W_C67.1, W_R113.2, W_R114.1, W_R117.2, W_U30.3
Wheel/CS_ADC2: W_J9.8, W_R145.1, W_U26.9
Wheel/CS_DRV8316: W_J9.4, W_R144.1, W_U24.9
Wheel/DRV_AVDD: W_C48.1, W_C49.1, W_C52.1, W_C54.1, W_C56.1, W_C57.1, W_R82.1, W_R86.1, W_R87.1, W_R88.1, W_R98.1, W_U21.25, W_U21.37, W_U23.7, W_U23.10, W_U24.13, W_U24.14, W_U26.13, W_U26.14
Wheel/DRV_CS_LOCAL: W_R86.2, W_U21.36, W_U24.8
Wheel/DRV_FAULT_LOCAL_N: W_J9.15, W_R88.2, W_R89.1, W_U21.22
Wheel/DRV_INHA: W_R90.1, W_U21.27, W_U22.6
Wheel/DRV_INHB: W_R91.1, W_U21.29, W_U22.8
Wheel/DRV_INHC: W_R92.1, W_U21.31, W_U22.11
Wheel/DRV_MISO_LOCAL: W_J9.5, W_R87.2, W_U21.33
Wheel/DRV_MOSI_LOCAL: W_U21.34, W_U24.6
Wheel/DRV_SCLK_LOCAL: W_U21.35, W_U24.3
Wheel/GND: W_C41.2, W_C42.2, W_C43.2, W_C44.2, W_C45.2, W_C48.2, W_C49.2, W_C50.2, W_C51.2, W_C52.2, W_C54.2, W_C56.2, W_C57.2, W_C58.2, W_C59.2, W_C60.2, W_C61.2, W_C65.2, W_C66.2, W_C67.2, W_C68.2, W_C69.2, W_C90.2, W_D6.2, W_J9.1, W_J9.17, W_J11.2, W_Q4.2, W_Q5.2, W_R83.2, W_R84.2, W_R89.2, W_R90.2, W_R91.2, W_R92.2, W_R94.2, W_R95.2, W_R96.2, W_R97.2, W_R100.2, W_R105.2, W_R106.2, W_R107.2, W_R108.2, W_R109.2, W_R114.2, W_R120.2, W_R137.2, W_R138.2, W_R139.2, W_R140.2, W_R144.2, W_R145.2, W_R146.2, W_TP37.1, W_U21.2, W_U21.4, W_U21.12, W_U21.15, W_U21.18, W_U21.26, W_U21.41, W_U22.7, W_U23.9, W_U23.17, W_U24.1, W_U24.4, W_U24.7, W_U24.10, W_U24.12, W_U26.1, W_U26.4, W_U26.7, W_U26.10, W_U26.12, W_U30.2, W_U31.2
Wheel/MOTOR_SPI_MOSI: W_J9.7, W_R97.1, W_U26.5
Wheel/MOTOR_SPI_SCLK: W_J9.6, W_R96.1, W_U26.2
Wheel/SPI_MOSI: W_J9.3, W_R95.1, W_U24.5
Wheel/SPI_SCLK: W_J9.2, W_R94.1, W_U24.2
Wheel/WHEEL_BUCK_OUT: W_C50.1, W_R81.2, W_U21.3
Wheel/WHEEL_BUCK_SW: W_R81.1, W_U21.5
Wheel/WHEEL_CP: W_C46.1, W_U21.8
Wheel/WHEEL_CPH: W_C47.1, W_U21.7
Wheel/WHEEL_CPL: W_C47.2, W_U21.6
Wheel/WHEEL_DRVOFF: W_Q4.3, W_R82.2, W_U21.21
Wheel/WHEEL_I_A: W_C59.1, W_R102.2, W_U23.15
Wheel/WHEEL_I_B: W_C60.1, W_R103.2, W_U23.16
Wheel/WHEEL_I_C: W_C61.1, W_R104.2, W_U23.1
Wheel/WHEEL_PHASE_A: W_J5.1, W_U21.13, W_U21.14
Wheel/WHEEL_PHASE_B: W_J5.2, W_U21.16, W_U21.17
Wheel/WHEEL_PHASE_C: W_J5.3, W_U21.19, W_U21.20
Wheel/WHEEL_PWM_A: W_J9.10, W_R138.1, W_U22.4
Wheel/WHEEL_PWM_B: W_J9.11, W_R139.1, W_U22.9
Wheel/WHEEL_PWM_C: W_J9.12, W_R140.1, W_U22.12
Wheel/WHEEL_RUN_EN: W_Q4.1, W_R83.1, W_U21.28, W_U21.30, W_U21.32, W_U22.3, W_U22.5, W_U22.10, W_U22.13
Wheel/WHEEL_RUN_REQ: W_J9.14, W_R137.1, W_U22.2
Wheel/WHEEL_SOA: W_R102.1, W_U21.40
Wheel/WHEEL_SOB: W_R103.1, W_U21.39
Wheel/WHEEL_SOC: W_R104.1, W_U21.38
